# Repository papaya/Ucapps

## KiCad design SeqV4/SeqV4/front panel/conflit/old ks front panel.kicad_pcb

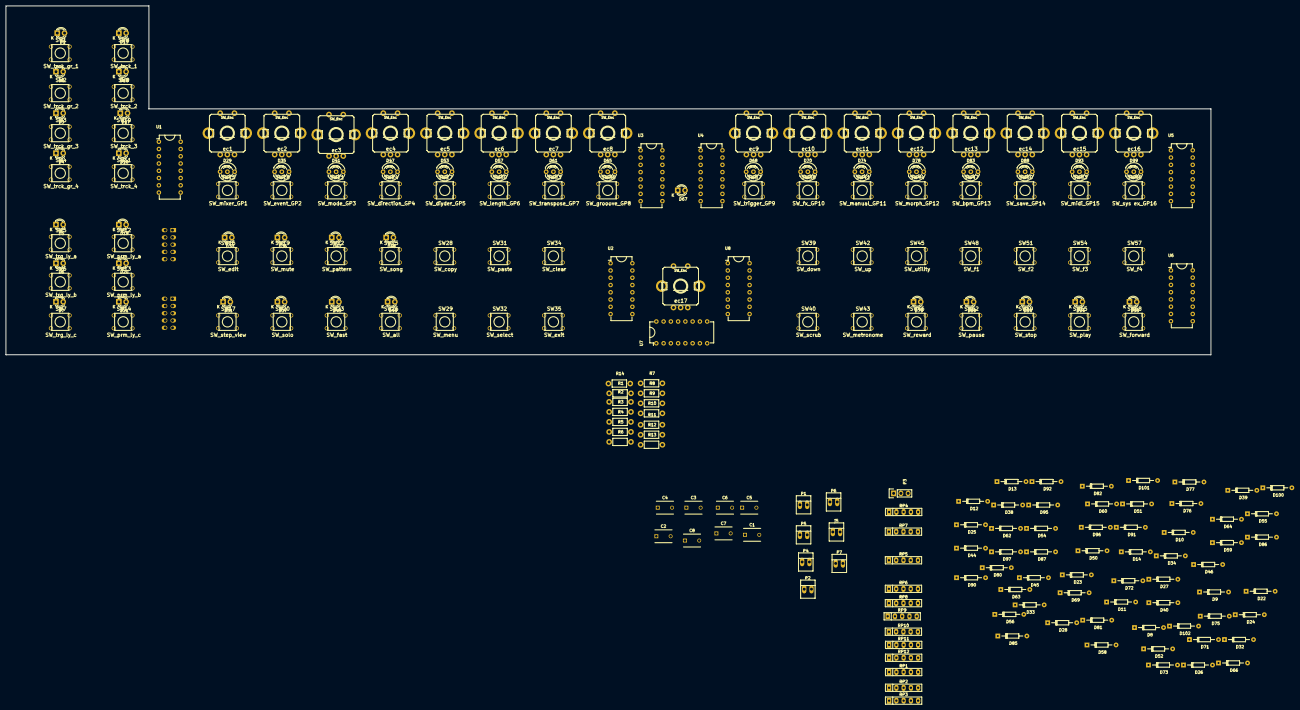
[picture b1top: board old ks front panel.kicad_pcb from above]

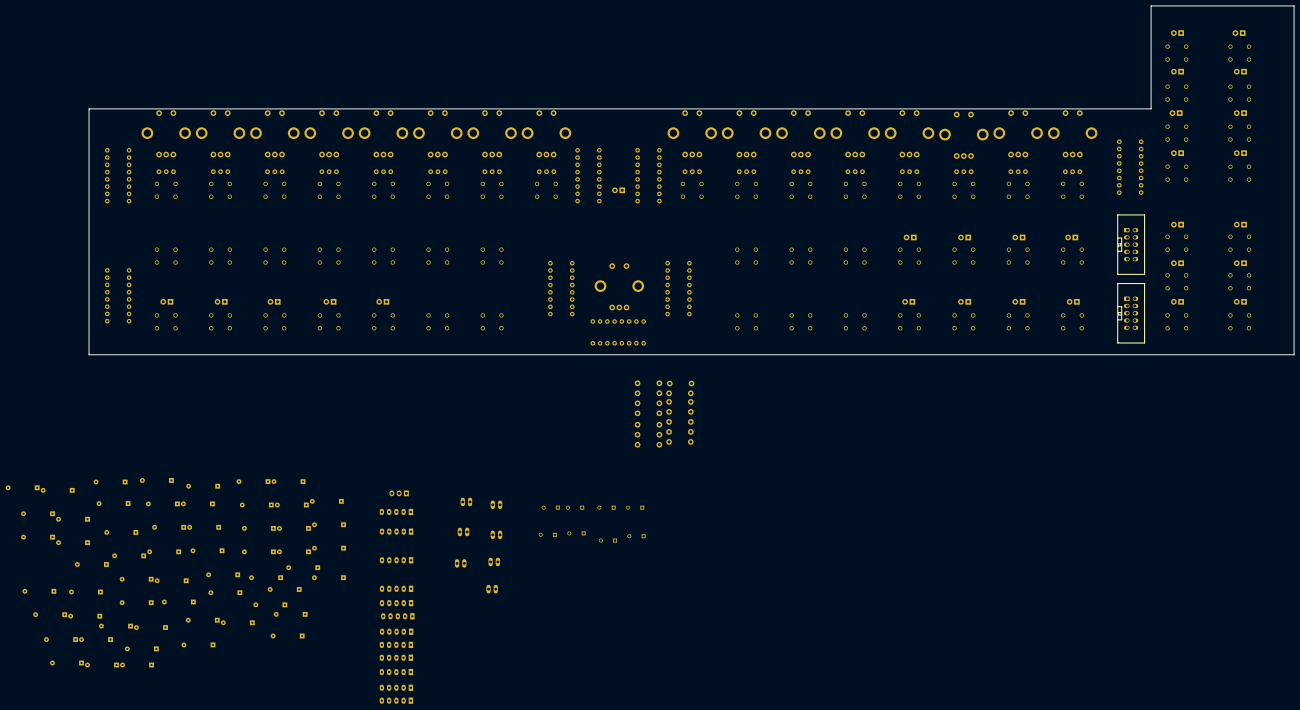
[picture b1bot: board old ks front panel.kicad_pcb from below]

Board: 2 copper layers, 421.5 x 122.0 mm, 229 parts (2 on the bottom side), 162 nets, no tracks yet.

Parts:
C1, C2, C3, C4, C5, C6, C7, C8: C; C_Disc_D6_P5
D1: LED trck gr 1; LED-3MM
D2: LED trck gr 2; LED-3MM
D3: LED_trck_gr_3; LED-3MM
D4: LED_trck_gr_4; LED-3MM
D5: LED_trg_ly_a; LED-3MM
D6: LED_trg_ly_b; LED-3MM
D7: LED_trg_ly_c; LED-3MM
D8, D9, D10, D11, D12, D13, D14, D22, D23, D24, D25, D26, D27, D28, D32, D33, D34, D38, D39, D40, D44, D45, D46, D50, D51, D52, D54, D55, D56, D58, D59, D60, D62, D63, D64, D66, D69, D71, D72, D73, D75, D76, D77, D80, D81, D82, D85, D86, D87, D90, D91, D92, D95, D96, D97, D100, D101, D102: D; Diode_DO-35_SOD27_Horizontal_RM10
D15: LED trck 1; LED-3MM
D16: LED trck 2; LED-3MM
D17: LED trck 3; LED-3MM
D18: LED trck 4; LED-3MM
D19: LED_prm_ly_a; LED-3MM
D20: LED_prm_ly_b; LED-3MM
D21: LED_prm_ly_c; LED-3MM
D29: Led_gp1; LED-5MM-3
D30: LED edit; LED-3MM
D31: LED step view; LED-3MM
D35: Led_gp2; LED-5MM-3
D36: LED mute; LED-3MM
D37: LED solo; LED-3MM
D41: Led_gp3; LED-5MM-3
D42: LED patern; LED-3MM
D43: LED fast; LED-3MM
D47: Led_gp4; LED-5MM-3
D48: LED song; LED-3MM
D49: LED all; LED-3MM
D53: Led_gp5; LED-5MM-3
D57: Led_gp6; LED-5MM-3
D61: Led_gp7; LED-5MM-3
D65: Led_gp8; LED-5MM-3
D67: LED beat; LED-3MM
D68: Led_gp9; LED-5MM-3
D70: Led_gp10; LED-5MM-3
D74: Led_gp11; LED-5MM-3
D78: Led_gp12; LED-5MM-3
D79: LED rwd; LED-3MM
D83: Led_gp13; LED-5MM-3
D84: LED stop; LED-3MM
D88: Led_gp14; LED-5MM-3
D89: LED pause; LED-3MM
D93: Led_gp15; LED-5MM-3
D94: LED play; LED-3MM
D98: LED fwd; LED-3MM
D99: Led_gp16; LED-5MM-3
P1, P2, P4, P5, P6, P7: CONN_01X02; PINHEAD1-2
P3: CONN_01X03; Pin_Header_Straight_1x03
R1, R2, R3, R4, R5, R6, R7, R8, R9, R10, R11, R12, R13, R14: R; Resistor_Horizontal_RM7mm
RP1, RP2, RP3, RP4, RP5, RP6, RP7, RP8, RP9, RP10, RP11, RP12: 5x10k; r-sil_5
SW1: SW_trck_gr_1; Tact6mm-PanasonicLTS
SW2: SW_trck_gr_2; Tact6mm-PanasonicLTS
SW3: SW_trck_gr_3; Tact6mm-PanasonicLTS
SW4: SW_trck_gr_4; Tact6mm-PanasonicLTS
SW5: SW_trg_ly_a; Tact6mm-PanasonicLTS
SW6: SW_trg_ly_b; Tact6mm-PanasonicLTS
SW7: SW_trg_ly_c; Tact6mm-PanasonicLTS
SW8: SW_trck_1; Tact6mm-PanasonicLTS
SW9: SW_trck_2; Tact6mm-PanasonicLTS
SW10: SW_trck_3; Tact6mm-PanasonicLTS
SW11: SW_trck_4; Tact6mm-PanasonicLTS
SW12: SW_prm_ly_a; Tact6mm-PanasonicLTS
SW13: SW_prm_ly_b; Tact6mm-PanasonicLTS
SW14: SW_prm_ly_c; Tact6mm-PanasonicLTS
SW15: SW_mixer_GP1; Tact6mm-PanasonicLTS
SW16: SW_edit; Tact6mm-PanasonicLTS
SW17: SW_step_view; Tact6mm-PanasonicLTS
SW18: SW_event_GP2; Tact6mm-PanasonicLTS
SW19: SW_mute; Tact6mm-PanasonicLTS
SW20: SW_solo; Tact6mm-PanasonicLTS
SW21: SW_mode_GP3; Tact6mm-PanasonicLTS
SW22: SW_pattern; Tact6mm-PanasonicLTS
SW23: SW_fast; Tact6mm-PanasonicLTS
SW24: SW_direction_GP4; Tact6mm-PanasonicLTS
SW25: SW_song; Tact6mm-PanasonicLTS
SW26: SW_all; Tact6mm-PanasonicLTS
SW27: SW_diyder_GP5; Tact6mm-PanasonicLTS
SW28: SW_copy; Tact6mm-PanasonicLTS
SW29: SW_menu; Tact6mm-PanasonicLTS
SW30: SW_length_GP6; Tact6mm-PanasonicLTS
SW31: SW_paste; Tact6mm-PanasonicLTS
SW32: SW_select; Tact6mm-PanasonicLTS
SW33: SW_transpose_GP7; Tact6mm-PanasonicLTS
SW34: SW_clear; Tact6mm-PanasonicLTS
SW35: SW_exit; Tact6mm-PanasonicLTS
SW36: SW_grooove_GP8; Tact6mm-PanasonicLTS
SW37: SW_trigger_GP9; Tact6mm-PanasonicLTS
SW38: SW_fx_GP10; Tact6mm-PanasonicLTS
SW39: SW_down; Tact6mm-PanasonicLTS
SW40: SW_scrub; Tact6mm-PanasonicLTS
SW41: SW_manual_GP11; Tact6mm-PanasonicLTS
SW42: SW_up; Tact6mm-PanasonicLTS
SW43: SW_metronome; Tact6mm-PanasonicLTS
SW44: SW_morph_GP12; Tact6mm-PanasonicLTS
SW45: SW_utility; Tact6mm-PanasonicLTS
SW46: SW_reward; Tact6mm-PanasonicLTS
SW47: SW_bpm_GP13; Tact6mm-PanasonicLTS
SW48: SW_f1; Tact6mm-PanasonicLTS
SW49: SW_stop; Tact6mm-PanasonicLTS
SW50: SW_save_GP14; Tact6mm-PanasonicLTS
SW51: SW_f2; Tact6mm-PanasonicLTS
SW52: SW_pause; Tact6mm-PanasonicLTS
SW53: SW_midi_GP15; Tact6mm-PanasonicLTS
SW54: SW_f3; Tact6mm-PanasonicLTS
SW55: SW_play; Tact6mm-PanasonicLTS
SW56: SW_sys ex_GP16; Tact6mm-PanasonicLTS
SW57: SW_f4; Tact6mm-PanasonicLTS
SW58: SW_forward; Tact6mm-PanasonicLTS
U1, U3: 74HC595PWR; DIP-16_W7.62mm
U2, U4, U5, U6, U7, U8: 74HC165; DIP-16_W7.62mm
ec1, ec2, ec3, ec4, ec5, ec6, ec7, ec8, ec9, ec10, ec11, ec12, ec13, ec14, ec15, ec16, ec17: SW_Enc; PEC11-Switch
j1, j2: CONN_02X05; vasch_strip_5x2
j5: CONN_01X02; PINHEAD1-2

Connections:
+5V: C1.1, C2.1, C3.1, C4.1, C5.1, C6.1, C7.1, C8.1, P3.3, U1.10, U1.16, U2.16, U3.10, U3.16, U4.16, U5.16, U6.16, U7.16, U8.16, j1.3, j1.4, j2.3, j2.4, j5.1
/02: D36.1, D42.1, D43.1, D48.1, D49.1, R2.2
/011: D29.1, D53.1, D68.1, D83.1, R8.2
/012: D35.3, D57.3, D70.3, D88.3, R9.2
/I0: RP2.4, U2.11, ec4.P$A
/I1: RP2.3, U2.12, ec4.P$B
/I2: RP2.2, U2.13, ec3.P$A
/I3: RP2.1, U2.14, ec3.P$B
/I4: U2.3, ec2.P$A
/I5: U2.4, ec2.P$B
/I6: U2.5, ec1.P$A
/I7: U2.6, ec1.P$B
/I10: D32.2, D44.2, D54.2, D62.2, D69.2, D75.2, D85.2, D95.2, RP4.4, U4.11
/I11: D38.2, D50.2, D58.2, D66.2, D71.2, D80.2, D90.2, D100.2, RP4.3, U4.12
/I12: D39.2, D51.2, D59.2, D72.2, D81.2, D91.2, D101.2, RP4.2, U4.13
/I13: D33.2, D45.2, D55.2, D63.2, D76.2, D86.2, D96.2, RP4.1, U4.14
/I14: D40.2, D52.2, D60.2, D73.2, D82.2, D92.2, D102.2, U4.3
/I15: D34.2, D46.2, D56.2, D64.2, D77.2, D87.2, D97.2, U4.4
/I16: D8.2, D10.2, D12.2, D14.2, D22.2, D24.2, D26.2, D28.2, U4.5
/I17: D9.2, D11.2, D13.2, D23.2, D25.2, D27.2, U4.6
/I20: RP8.4, U6.11, ec8.P$A
/I21: RP8.3, U6.12, ec8.P$B
/I22: RP8.2, U6.13, ec7.P$A
/I23: RP8.1, U6.14, ec7.P$B
/I24: U6.3, ec6.P$A
/I25: U6.4, ec6.P$B
/I26: U6.5, ec5.P$A
/I27: U6.6, ec5.P$B
/I30: RP12.4, U8.11, ec13.P$A
/I31: RP12.3, U8.12, ec13.P$B
/I32: RP12.2, U8.13, ec12.P$A
/I33: RP12.1, U8.14, ec12.P$B
/I34: U8.3, ec11.P$A
/I35: U8.4, ec11.P$B
/I36: U8.5, ec10.P$A
/I37: U8.6, ec10.P$B
/I40: RP7.4, U5.11, ec17.P$A
/I41: RP7.3, U5.12, ec17.P$B
/I42: RP7.2, U5.13, ec16.P$A
/I43: RP7.1, U5.14, ec16.P$B
/I44: U5.3, ec15.P$A
/I45: U5.4, ec15.P$B
/I46: U5.5, ec14.P$A
/I47: U5.6, ec14.P$B
/I50: RP11.4, U7.11
/I51: RP11.3, U7.12
/I52: RP11.2, U7.13
/I53: RP11.1, U7.14
/I54: U7.3, ec9.P$A
/I55: U7.4, ec9.P$B
/I56: U7.5, ec9.P$2
/I57: U7.6, ec1.P$2, ec2.P$2, ec3.P$2, ec4.P$2, ec5.P$2, ec6.P$2, ec7.P$2, ec8.P$2, ec10.P$2, ec11.P$2, ec12.P$2, ec13.P$2, ec14.P$2, ec15.P$2, ec16.P$2, ec17.P$2
/O0: D1.1, D2.1, D3.1, D4.1, D61.2, D65.2, SW1.2, SW2.2, SW31.2, SW32.2, SW33.2, SW34.2, SW35.2, SW36.2, U1.15
/O1: D15.1, D17.1, D53.2, D57.2, SW8.2, SW9.2, SW25.2, SW26.2, SW27.2, SW28.2, SW29.2, SW30.2
/O2: D37.1, D41.2, D47.2, SW3.2, SW4.2, SW19.2, SW20.2, SW21.2, SW22.2, SW23.2, SW24.2
/O3: D16.1, D18.1, D29.2, D30.1, D35.2, R3.2, SW10.2, SW11.2, SW15.2, SW16.2, SW17.2, SW18.2
/O4: D19.1, D20.1, D21.1, D68.2, D70.2, R4.2, SW12.2, SW13.2, SW37.1, SW38.1, SW39.1, SW40.1, SW42.1, SW43.1
/O5: D31.1, D74.2, D78.2, D84.1, R5.2, SW14.2, SW41.1, SW44.1, SW45.1, SW46.1, SW48.1, SW49.1
/O6: D5.1, D6.1, D7.1, D79.1, D83.2, D88.2, D89.1, R6.2, SW5.2, SW6.2, SW47.1, SW50.1, SW51.1, SW52.1, SW54.1, SW55.1
/O7: D67.1, D93.2, D94.1, D98.1, D99.2, R7.2, SW7.2, SW53.1, SW56.1, SW57.1, SW58.1
/O10: D29.3, D53.3, D68.3, D83.3, U3.15
/O13: D35.1, D57.1, D70.1, D88.1, R10.2
/O14: D1.2, D30.2, D36.2, D41.3, D42.2, D61.3, D74.3, D84.2, D89.2, D93.3, D94.2, R11.2
/O15: D2.2, D5.2, D16.2, D17.2, D19.2, D41.1, D48.2, D61.1, D74.1, D79.2, D93.1, D98.2, R12.2
/O16: D3.2, D6.2, D15.2, D18.2, D20.2, D31.2, D37.2, D43.2, D47.3, D65.3, D78.3, D99.3, R13.2
/O17: D4.2, D7.2, D21.2, D47.1, D49.2, D65.1, D67.2, D78.1, D99.1, R14.2
GND: C1.2, C2.2, C3.2, C4.2, C5.2, C6.2, C7.2, C8.2, P3.1, U1.8, U1.13, U2.8, U2.15, U3.8, U3.13, U4.8, U4.15, U5.8, U5.15, U6.8, U6.15, U7.8, U7.15, U8.8, U8.15, ec1.P$1, ec1.P$C, ec2.P$1, ec2.P$C, ec3.P$1, ec3.P$C, ec4.P$1, ec4.P$C, ec5.P$1, ec5.P$C, ec6.P$1, ec6.P$C, ec7.P$1, ec7.P$C, ec8.P$1, ec8.P$C, ec9.P$1, ec9.P$C, ec9.P$GN, ec10.P$1, ec10.P$C, ec11.P$1, ec11.P$C, ec12.P$1, ec12.P$C, ec13.P$1, ec13.P$C, ec14.P$1, ec14.P$C, ec15.P$1, ec15.P$C, ec16.P$1, ec16.P$C, ec17.P$1, ec17.P$C, j1.1, j1.2, j2.1, j2.2, j5.2
unnamed: D8.1, SW1.1
unnamed: D9.1, SW2.1
unnamed: D10.1, SW3.1
unnamed: D11.1, SW4.1
unnamed: D12.1, SW5.1
unnamed: D13.1, SW6.1
unnamed: D14.1, SW7.1
unnamed: D22.1, SW8.1
unnamed: D23.1, SW9.1
unnamed: D24.1, SW10.1
unnamed: D25.1, SW11.1
unnamed: D26.1, SW12.1
unnamed: D27.1, SW13.1
unnamed: D28.1, SW14.1
unnamed: D32.1, SW15.1
unnamed: D33.1, SW16.1
unnamed: D34.1, SW17.1
unnamed: D38.1, SW18.1
unnamed: D39.1, SW19.1
unnamed: D40.1, SW20.1
unnamed: D44.1, SW21.1
unnamed: D45.1, SW22.1
unnamed: D46.1, SW23.1
unnamed: D50.1, SW24.1
unnamed: D51.1, SW25.1
unnamed: D52.1, SW26.1
unnamed: D54.1, SW27.1
unnamed: D55.1, SW28.1
unnamed: D56.1, SW29.1
unnamed: D58.1, SW30.1
unnamed: D59.1, SW31.1
unnamed: D60.1, SW32.1
unnamed: D62.1, SW33.1
unnamed: D63.1, SW34.1
unnamed: D64.1, SW35.1
unnamed: D66.1, SW36.1
unnamed: D69.1, SW37.2
unnamed: D71.1, SW38.2
unnamed: D72.1, SW39.2
unnamed: D73.1, SW40.2
unnamed: D75.1, SW41.2
unnamed: D76.1, SW42.2
unnamed: D77.1, SW43.2
unnamed: D80.1, SW44.2
unnamed: D81.1, SW45.2
unnamed: D82.1, SW46.2
unnamed: D85.1, SW47.2
unnamed: D86.1, SW48.2
unnamed: D87.1, SW49.2
unnamed: D90.1, SW50.2
unnamed: D91.1, SW51.2
unnamed: D92.1, SW52.2
unnamed: D95.1, SW53.2
unnamed: D96.1, SW54.2
unnamed: D97.1, SW55.2
unnamed: D100.1, SW56.2
unnamed: D101.1, SW57.2
unnamed: D102.1, SW58.2
unnamed: P1.1, U2.7
unnamed: P2.1, U5.7
unnamed: P3.2, RP1.1, RP1.2, RP1.3, RP1.4, RP1.5, RP3.1, RP3.2, RP3.3, RP3.4, RP3.5, RP5.1, RP5.2, RP5.3, RP5.4, RP5.5, RP9.1, RP9.2, RP9.3, RP9.4, RP9.5, RP10.1, RP10.2, RP10.3, RP10.4, RP10.5
unnamed: P4.1, U4.7
unnamed: P5.1, U6.7
unnamed: P6.1, U7.7
unnamed: P7.1, U8.7
unnamed: R1.1, U1.1
unnamed: R2.1, U1.2
unnamed: R3.1, U1.3
unnamed: R4.1, U1.4
unnamed: R5.1, U1.5
unnamed: R6.1, U1.6
unnamed: R7.1, U1.7
unnamed: R8.1, U3.1
unnamed: R9.1, U3.2
unnamed: R10.1, U3.3
unnamed: R11.1, U3.4
unnamed: R12.1, U3.5
unnamed: R13.1, U3.6
unnamed: R14.1, U3.7
unnamed: RP2.5, U2.10, U4.9
unnamed: RP4.5, U4.10, U6.9
unnamed: RP6.1, RP6.2, RP6.3, RP6.4, RP6.5
unnamed: RP7.5, U5.10, j2.5
unnamed: RP8.5, U6.10, U8.9
unnamed: RP11.5, U5.9, U7.10
unnamed: RP12.5, U7.9, U8.10
unnamed: U1.9, U3.14
unnamed: U1.11, U2.2, U3.12, U4.2, j1.7, j1.8, j2.7, j2.8
unnamed: U1.12, U2.1, U3.11, U4.1, j1.10, j2.10
unnamed: U1.14, j1.6
unnamed: U2.9, j1.5
unnamed: U3.9, j2.6
unnamed: U5.1, U6.1, U7.1, U8.1
unnamed: U5.2, U6.2, U7.2, U8.2
unnamed: ec1.P$GN, ec2.P$GN, ec3.P$GN, ec4.P$GN, ec5.P$GN, ec6.P$GN, ec7.P$GN, ec8.P$GN, ec10.P$GN, ec11.P$GN, ec12.P$GN, ec13.P$GN, ec14.P$GN, ec15.P$GN, ec16.P$GN, ec17.P$GN

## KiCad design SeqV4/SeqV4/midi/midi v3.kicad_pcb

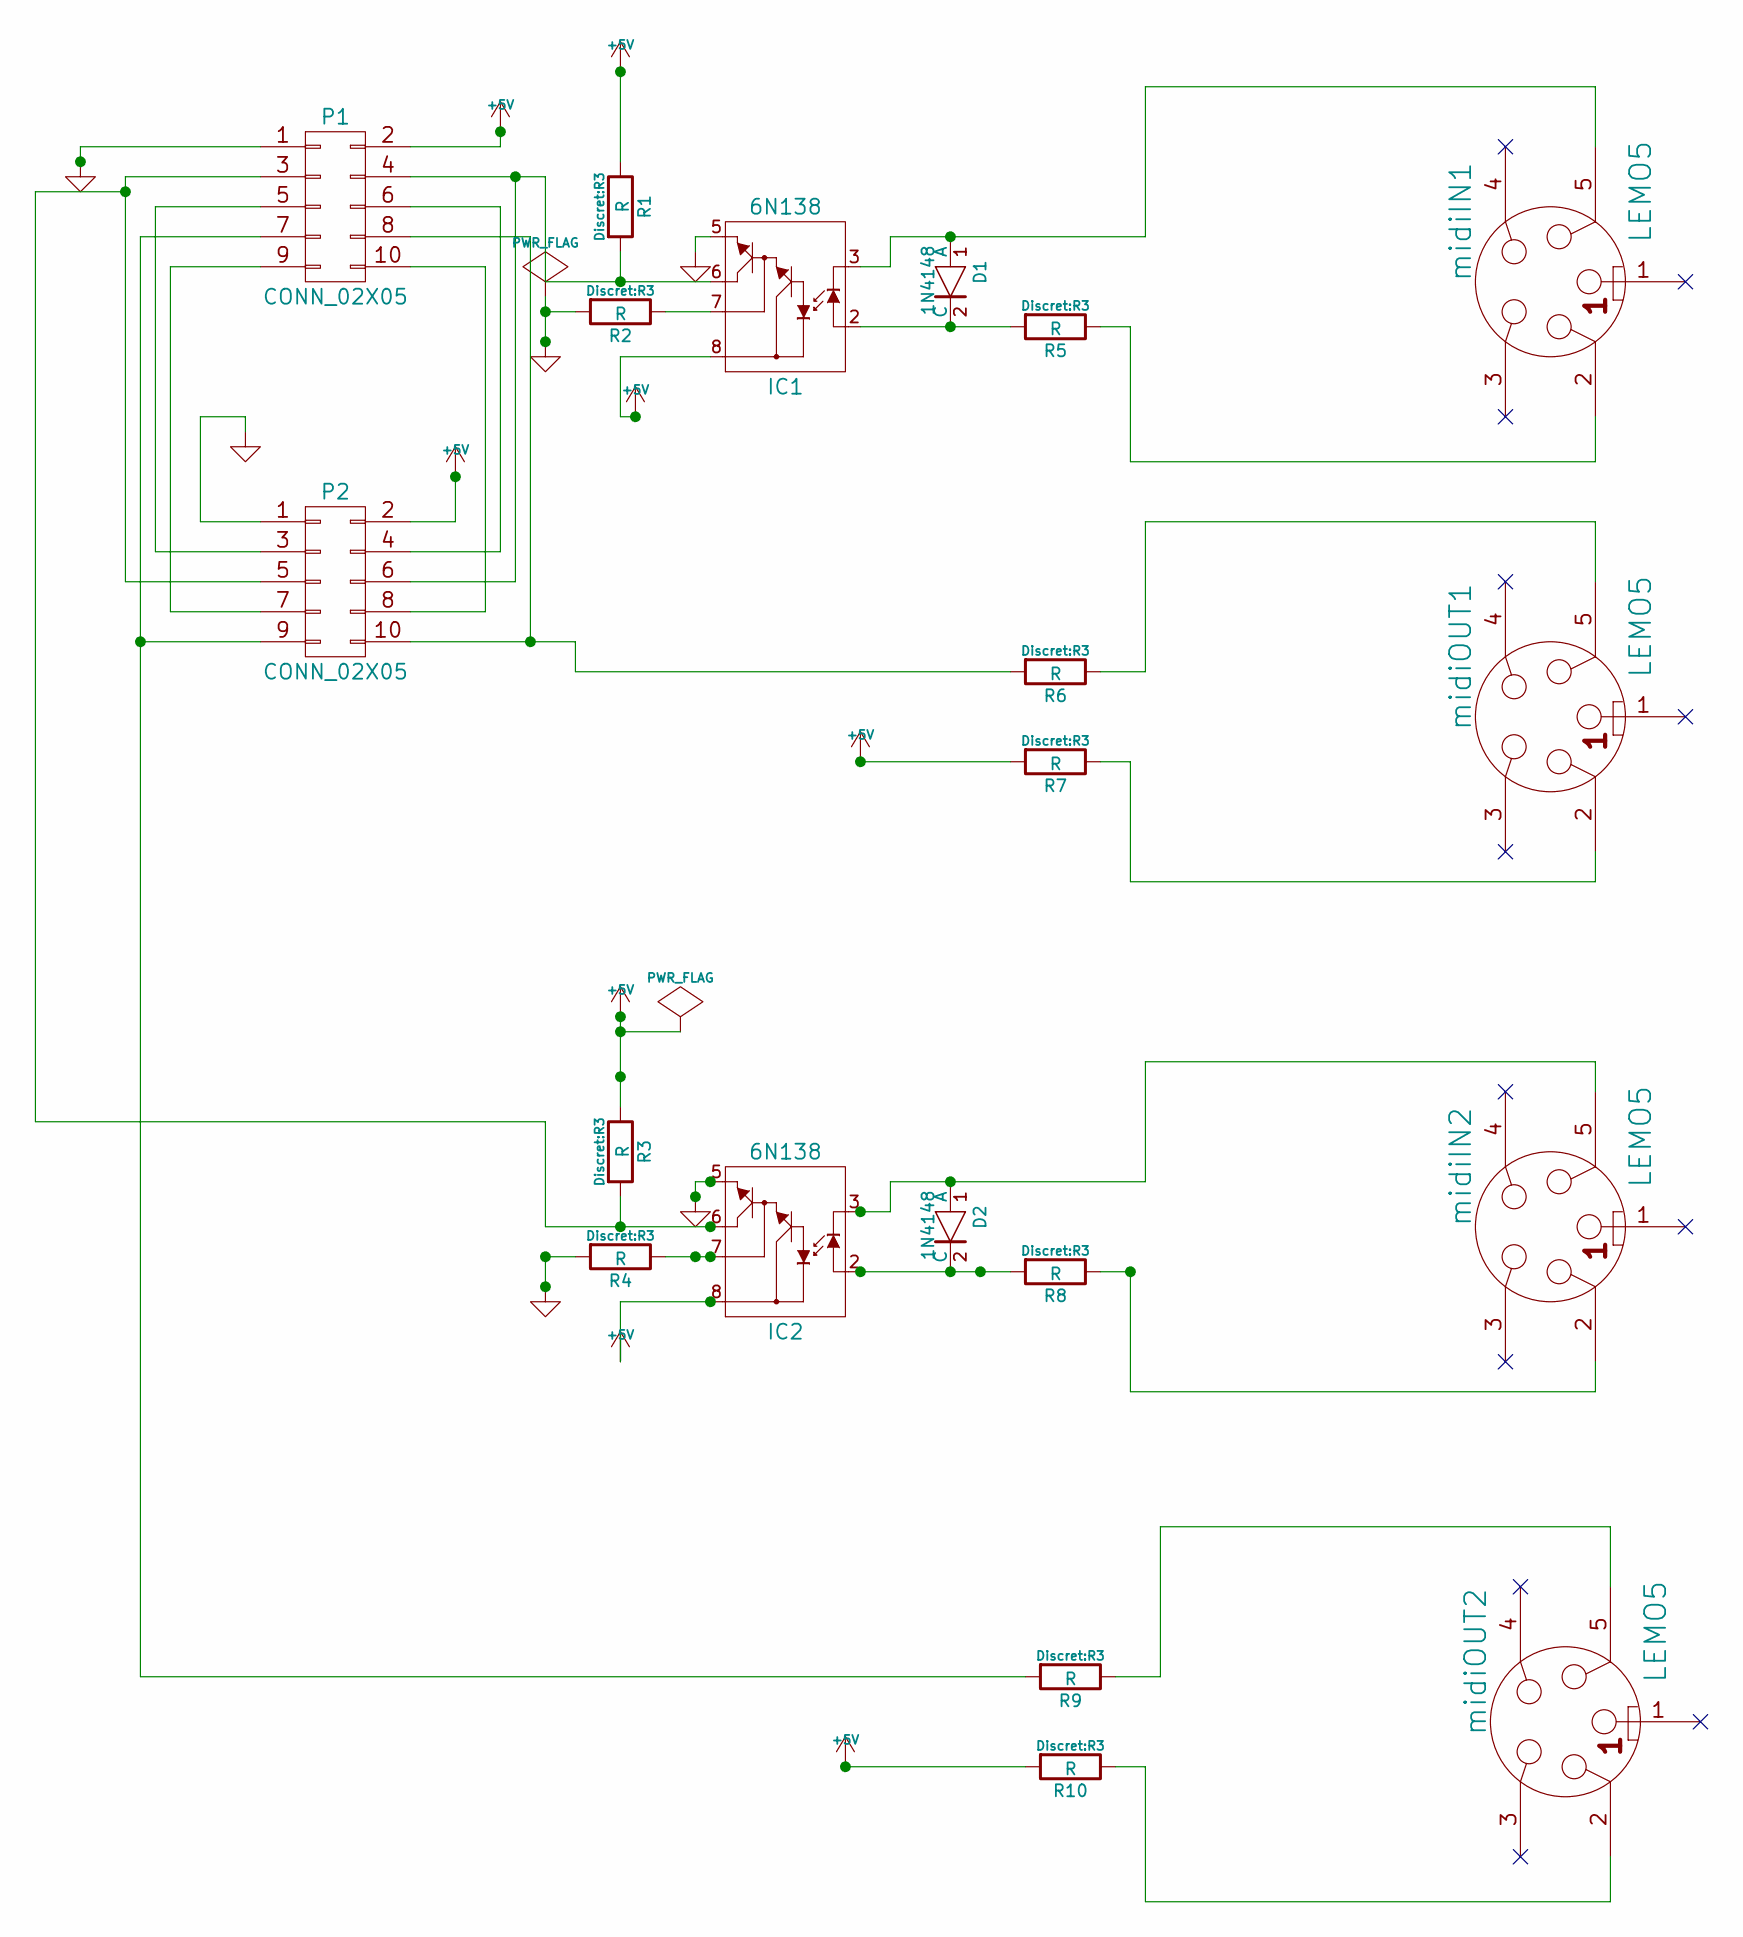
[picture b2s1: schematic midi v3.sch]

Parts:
D1, D2: 1N4148; D3
IC1, IC2: 6N138; DIP-8_W7.62mm
P1, P2: CONN_02X05; vasch_strip_5x2
R1, R2, R3, R4, R5, R6, R7, R8, R9, R10: R; R3
midiIN1, midiIN2: LEMO5; din-5
midiOUT1, midiOUT2: LEMO5; din-5

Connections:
+5V: IC1.8 (Vcc), IC2.8 (Vcc), P1.2, P2.2, R1.1, R3.1, R7.2, R10.2
GND: IC1.5 (GND), IC2.5 (GND), P1.1, P2.1, R2.2, R4.2
unnamed: D1.1 (A), IC1.3 (K), midiIN1.5
unnamed: D1.2 (C), IC1.2 (A), R5.2
unnamed: D2.1 (A), IC2.3 (K), midiIN2.5
unnamed: D2.2 (C), IC2.2 (A), R8.2
unnamed: IC1.6 (Vo), P1.4, P2.6, R1.2
unnamed: IC1.7 (Vb), R2.1
unnamed: IC2.6 (Vo), P1.3, P2.5, R3.2
unnamed: IC2.7 (Vb), R4.1
unnamed: P1.5, P2.3
unnamed: P1.6, P2.4
unnamed: P1.7, P2.9, R9.2
unnamed: P1.8, P2.10, R6.2
unnamed: P1.9, P2.7
unnamed: P1.10, P2.8
unnamed: R5.1, midiIN1.2
unnamed: R6.1, midiOUT1.5
unnamed: R7.1, midiOUT1.2
unnamed: R8.1, midiIN2.2
unnamed: R9.1, midiOUT2.5
unnamed: R10.1, midiOUT2.2

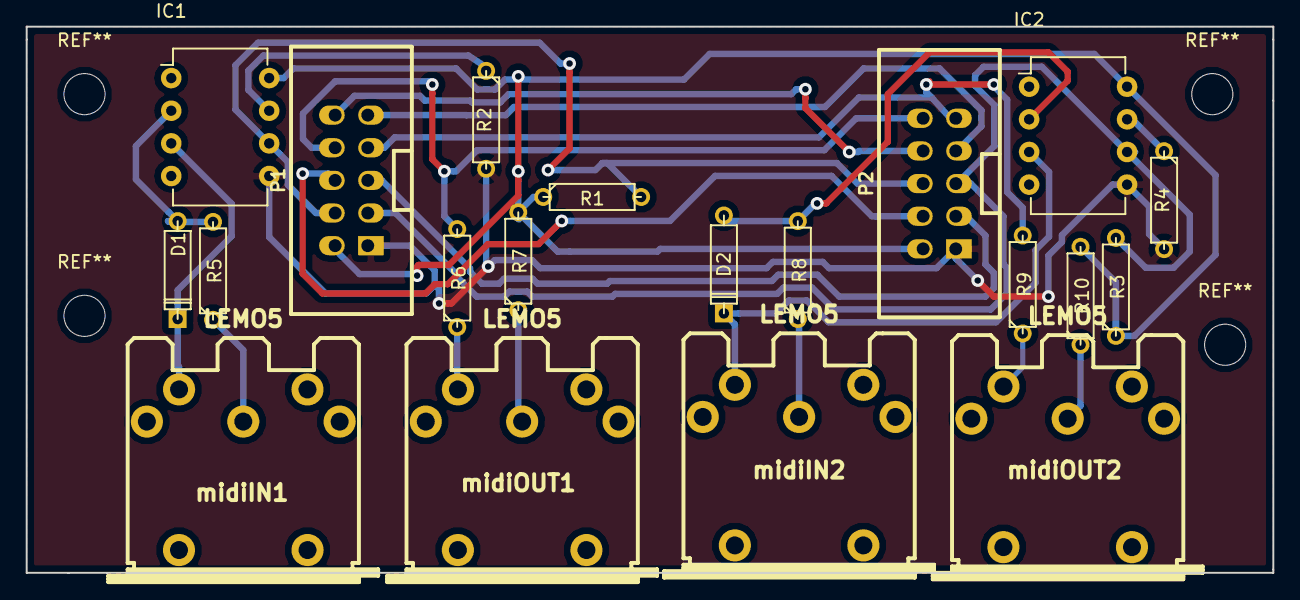
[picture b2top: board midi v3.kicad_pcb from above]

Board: 2 copper layers, 97.0 x 42.5 mm, 20 parts (0 on the bottom side), 22 nets.
